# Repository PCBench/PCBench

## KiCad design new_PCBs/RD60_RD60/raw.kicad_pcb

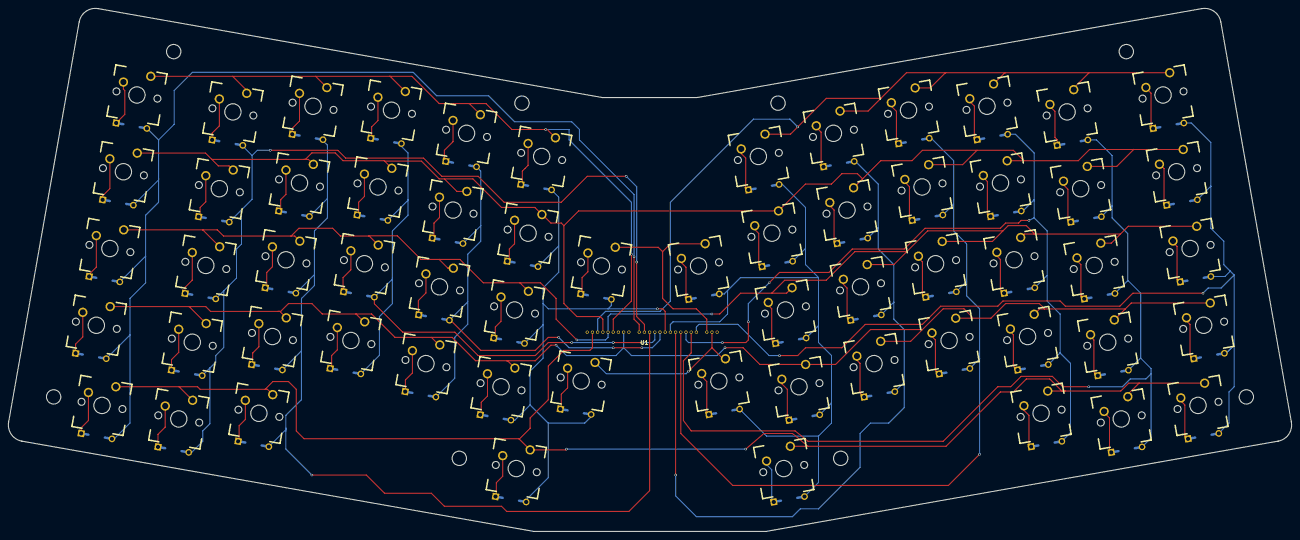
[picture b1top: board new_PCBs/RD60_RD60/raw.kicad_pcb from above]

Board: 2 copper layers, 313.6 x 127.8 mm, 61 parts (0 on the bottom side), 80 nets.

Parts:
U1: k270
U2, U3, U4, U5, U6, U7, U8, U9, U10, U11, U12, U13, U14, U15, U16, U17, U18, U19, U20, U21, U22, U23, U24, U25, U26, U27, U28, U29, U30, U31, U32, U33, U34, U35, U36, U37, U38, U39, U40, U41, U42, U43, U44, U45, U46, U47, U48, U49, U50, U51, U52, U53, U54, U55, U56, U57, U58, U59, U60, U61: mx1a

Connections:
2: U1.2, U6.1, U11.1, U16.1, U29.1, U34.1, U51.1, U56.1, U61.1
3: U1.3, U35.1, U39.1, U43.1, U47.1, U52.1, U57.1
4: U1.4, U3.1, U8.1, U13.1, U18.1, U22.1, U26.1, U36.1, U40.1, U44.1, U48.1, U53.1, U58.1
5: U1.5, U4.1, U9.1, U14.1, U19.1, U23.1, U27.1, U37.1, U41.1, U45.1, U49.1, U54.1, U59.1
6: U1.6, U2.1, U7.1, U12.1, U17.1, U21.1, U25.1
8: U1.8, U5.1, U10.1, U15.1, U20.1, U24.1, U28.1, U38.1, U42.1, U46.1, U50.1, U55.1, U60.1
10: U1.10, U2.2, U3.2, U4.2, U5.2, U6.2
11: U1.11, U7.2, U8.2, U9.2, U10.2, U11.2
12: U1.12, U12.2, U13.2, U14.2, U15.2, U16.2
13: U1.13, U17.2, U18.2, U19.2, U20.2
14: U1.14, U21.2, U22.2, U23.2, U24.2
15: U1.15, U25.2, U26.2, U27.2, U28.2, U29.2, U30.2, U31.2
16: U1.16, U32.2, U33.2, U34.2, U35.2, U36.2, U37.2, U38.2
17: U1.17, U39.2, U40.2, U41.2, U42.2
18: U1.18, U43.2, U44.2, U45.2, U46.2
19: U1.19, U47.2, U48.2, U49.2, U50.2, U51.2
20: U1.20, U52.2, U53.2, U54.2, U55.2, U56.2
21: U1.21, U57.2, U58.2, U59.2, U60.2, U61.2
22: U1.22, U30.1, U32.1
23: U1.23, U31.1, U33.1
unnamed: U2.3, U2.4
unnamed: U3.3, U3.4
unnamed: U4.3, U4.4
unnamed: U5.3, U5.4
unnamed: U6.3, U6.4
unnamed: U7.3, U7.4
unnamed: U8.3, U8.4
unnamed: U9.3, U9.4
unnamed: U10.3, U10.4
unnamed: U11.3, U11.4
unnamed: U12.3, U12.4
unnamed: U13.3, U13.4
unnamed: U14.3, U14.4
unnamed: U15.3, U15.4
unnamed: U16.3, U16.4
unnamed: U17.3, U17.4
unnamed: U18.3, U18.4
unnamed: U19.3, U19.4
unnamed: U20.3, U20.4
unnamed: U21.3, U21.4
unnamed: U22.3, U22.4
unnamed: U23.3, U23.4
unnamed: U24.3, U24.4
unnamed: U25.3, U25.4
unnamed: U26.3, U26.4
unnamed: U27.3, U27.4
unnamed: U28.3, U28.4
unnamed: U29.3, U29.4
unnamed: U30.3, U30.4
unnamed: U31.3, U31.4
unnamed: U32.3, U32.4
unnamed: U33.3, U33.4
unnamed: U34.3, U34.4
unnamed: U35.3, U35.4
unnamed: U36.3, U36.4
unnamed: U37.3, U37.4
unnamed: U38.3, U38.4
unnamed: U39.3, U39.4
unnamed: U40.3, U40.4
unnamed: U41.3, U41.4
unnamed: U42.3, U42.4
unnamed: U43.3, U43.4
unnamed: U44.3, U44.4
unnamed: U45.3, U45.4
unnamed: U46.3, U46.4
unnamed: U47.3, U47.4
unnamed: U48.3, U48.4
unnamed: U49.3, U49.4
unnamed: U50.3, U50.4
unnamed: U51.3, U51.4
unnamed: U52.3, U52.4
unnamed: U53.3, U53.4
unnamed: U54.3, U54.4
unnamed: U55.3, U55.4
unnamed: U56.3, U56.4
unnamed: U57.3, U57.4
unnamed: U58.3, U58.4
unnamed: U59.3, U59.4
unnamed: U60.3, U60.4
unnamed: U61.3, U61.4

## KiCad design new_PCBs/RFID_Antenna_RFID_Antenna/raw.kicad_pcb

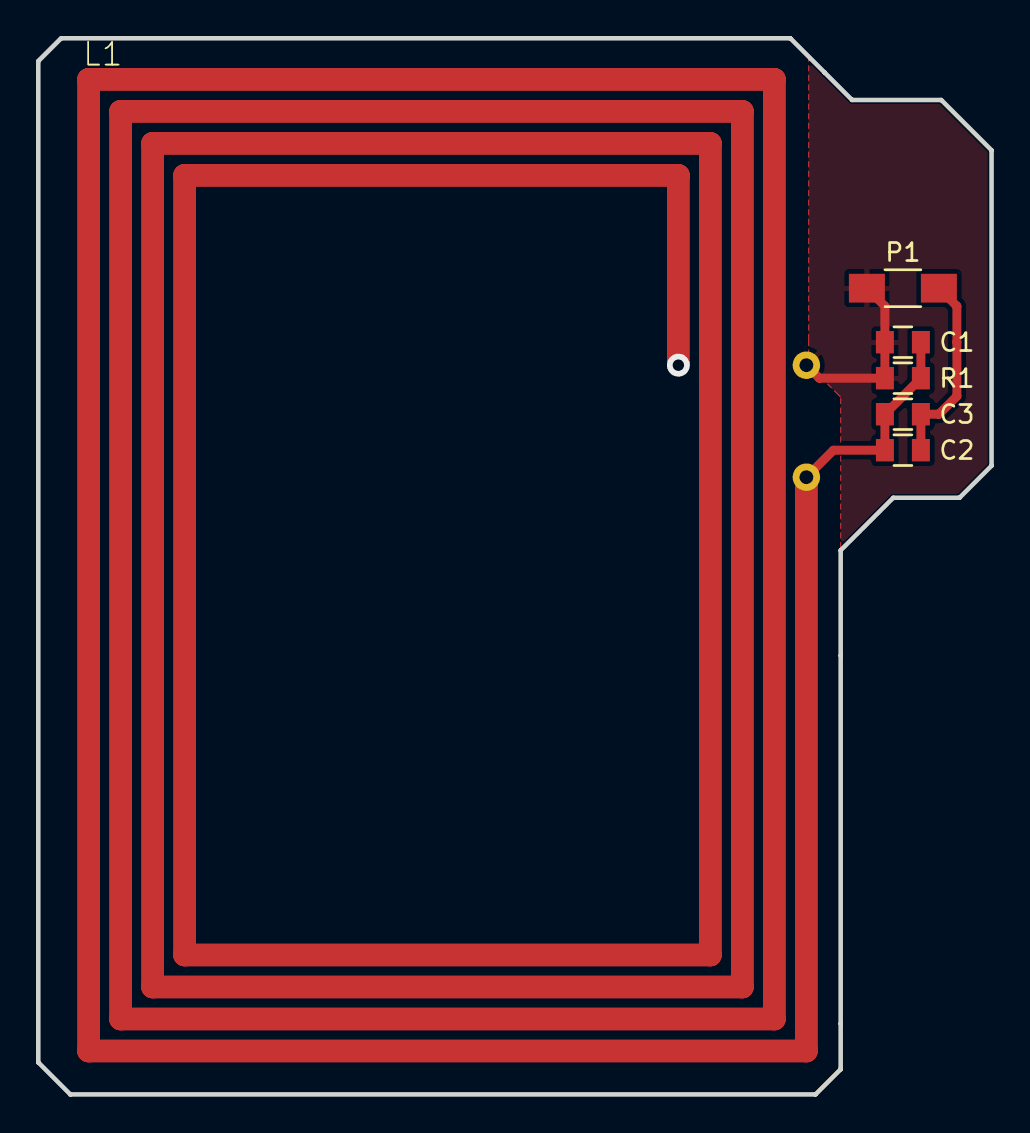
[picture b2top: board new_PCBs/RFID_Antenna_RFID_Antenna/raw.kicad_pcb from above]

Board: 2 copper layers, 53.0 x 58.7 mm, 6 parts (0 on the bottom side), 3 nets.

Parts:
C1, C2: 47p; C_0805
C3: 10p; C_0805
L1: 13.56 MHz Antenna; 13.56 RFID ANTENNA
P1: Coax; C_1206_HandSoldering
R1: 1k; C_0805

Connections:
unnamed: C1.1, L1.2, P1.2, R1.1
unnamed: C1.2, C2.1, C3.1, L1.1, R1.2
unnamed: C2.2, C3.2, P1.1

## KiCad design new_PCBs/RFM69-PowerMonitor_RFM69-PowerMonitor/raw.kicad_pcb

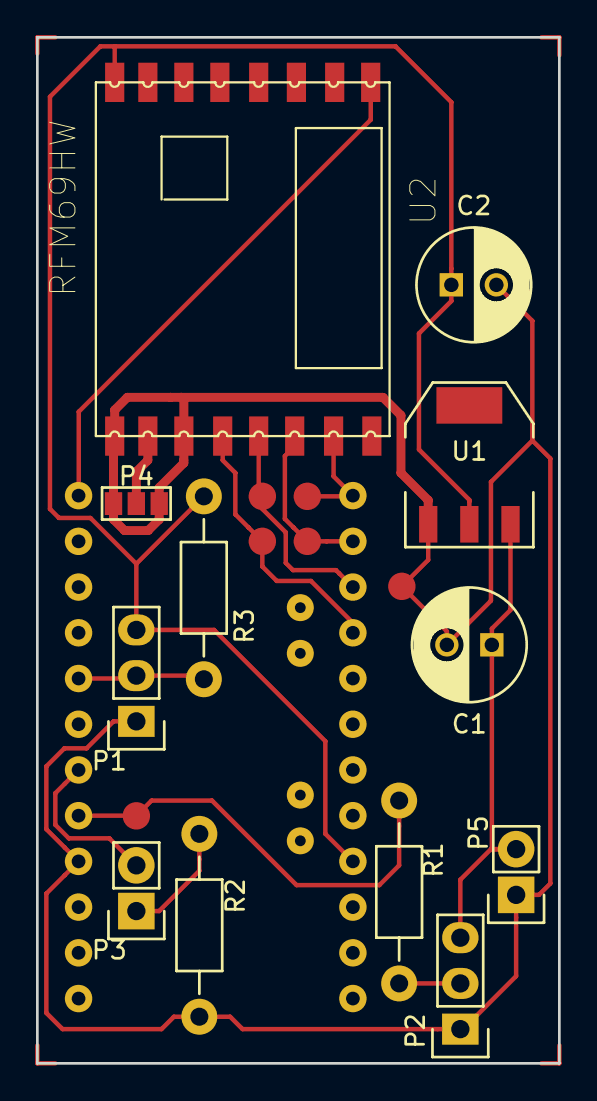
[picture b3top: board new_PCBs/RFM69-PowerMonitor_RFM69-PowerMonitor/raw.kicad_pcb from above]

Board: 2 copper layers, 29.0 x 57.0 mm, 13 parts (1 on the bottom side), 14 nets.

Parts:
C1: 10uF; C_Radial_D6.3_L11.2_P2.5
C2: 100uF; C_Radial_D6.3_L11.2_P2.5
P1: 1WIRE; Pin_Header_Straight_1x03
P2: CONN_PIR; Pin_Header_Straight_1x03
P3: MTR; Pin_Header_Straight_1x02
P4: ANT; GS3
P5: CONN_PWR; Pin_Header_Straight_1x02
R1, R2: 470; Resistor_Horizontal_RM10mm
R3: 2.2k; Resistor_Horizontal_RM10mm
U1: AP1117D33; SOT-223
U2: RFM69HW; RFM
uP1: ARDUPROMINI-6; ArduProMini-6

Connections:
+5V: C1.1, P2.3, P5.2, U1.3
GND: C1.2, C2.2, P1.1, P2.1, P4.1, P4.3, P5.1, R2.1, U1.1, U2.GNDA, U2.GNDB, uP1.10
unnamed: C2.1, P1.3, R3.1, U1.2, U2.VCC, uP1.22
unnamed: P1.2, R3.2, uP1.14
unnamed: P2.2, R1.2
unnamed: P3.1, R2.2
unnamed: P3.2, uP1.12
unnamed: P4.2, U2.ANT
unnamed: R1.1, uP1.11
unnamed: U2.MISO, uP1.28
unnamed: U2.MOSI, uP1.29
unnamed: U2.NSS, uP1.30
unnamed: U2.RESE, uP1.18
unnamed: U2.SCK, uP1.27

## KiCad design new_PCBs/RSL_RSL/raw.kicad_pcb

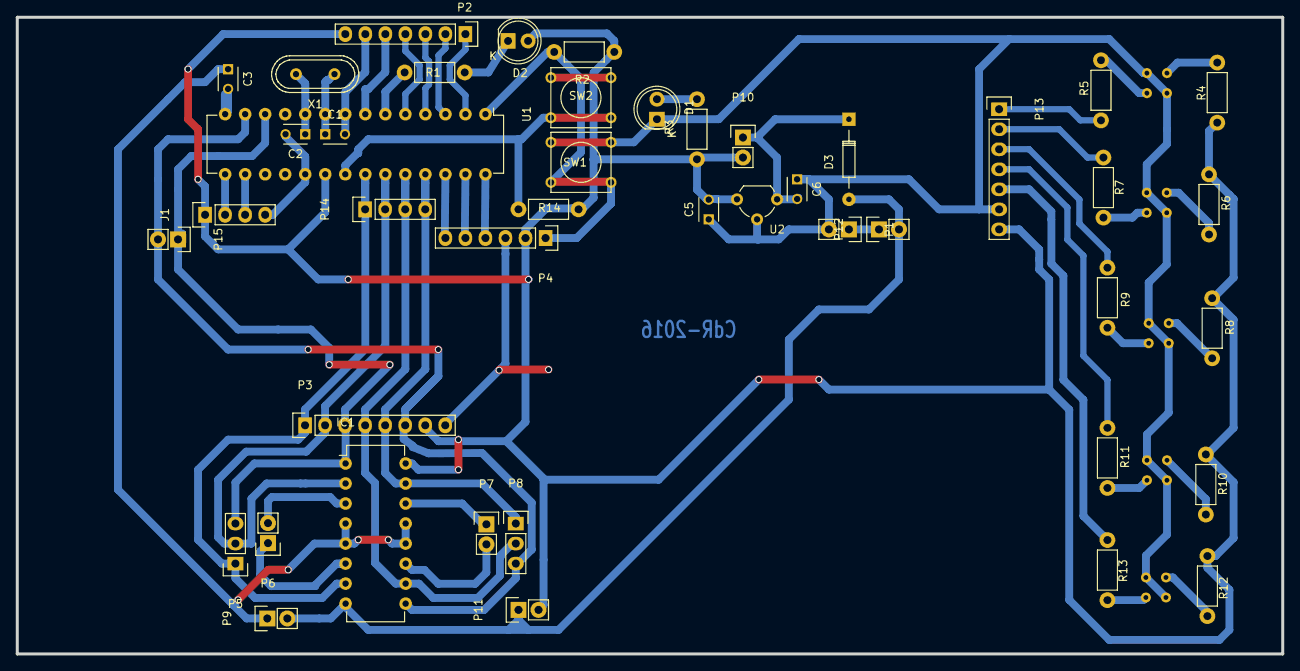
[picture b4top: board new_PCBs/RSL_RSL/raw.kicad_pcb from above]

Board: 2 copper layers, 160.5 x 80.8 mm, 49 parts (0 on the bottom side), 43 nets.

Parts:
C1: C-crsital; C_Disc_D3_P2.5
C2: C-cristal; C_Disc_D3_P2.5
C3: C; C_Disc_D3_P2.5
C5, C6: C-reg; C_Disc_D3_P2.5
D1: PWR; LED-5MM
D2: RUN; LED-5MM
D3: D_Small; Diode_DO-35_SOD27_Horizontal_RM10
IC1: L293D; DIP-16_W7.62mm
J1: USB; Pin_Header_Straight_1x04
P1: Alimentacion; Pin_Header_Straight_1x02
P2, P13: Pines_Sensores; Socket_Strip_Straight_1x07
P3: Pines_ Driver_M; Socket_Strip_Straight_1x08
P4: pickit; Socket_Strip_Straight_1x06
P5: 2A-1A-1.2E; Pin_Header_Straight_1x03
P6: motor1; Pin_Header_Straight_1x02
P7: motor2; Pin_Header_Straight_1x02
P8: E3.4-3A-4A; Pin_Header_Straight_1x03
P9: alimtacionMOTORES; Pin_Header_Straight_1x02
P10: BAT; Pin_Header_Straight_1x02
P11: jp1; Pin_Header_Straight_1x02
P12: PWRSW; Pin_Header_Straight_1x02
P14: Ctrl_Dir; Pin_Header_Straight_1x04
P15: PWM; Pin_Header_Straight_1x02
R1: 470; Resistor_Horizontal_RM7mm
R2: 10K; Resistor_Horizontal_RM7mm
R3, R4, R5, R6, R7, R8, R9, R10, R11, R12, R13, R14: R; Resistor_Horizontal_RM7mm
SW1: reset; SW_PUSH_SMALL
SW2: int0; SW_PUSH_SMALL
U1: PIC18F2550; DIP-28_W7.62mm
U2: 7805; TO-92_Molded_Wide
U3, U4, U5, U6, U7: CNY70; cny70-4
X1: CRYSTAL; Crystal_HC49-U_Vertical

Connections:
/0: R14.2, SW2.1, U1.21
/5: P4.6, U1.26
/6: P4.5, U1.27
/7: P4.4, U1.28
/D+: J1.3, U1.16
/D-: J1.2, U1.15
/driver_motores/1A: IC1.2, P3.2, P5.2, P14.2, U1.23
/driver_motores/2A: IC1.7, P3.1, P5.1, P14.1, U1.22
/driver_motores/3A: IC1.10, P3.4, P8.2, P14.3, U1.24
/driver_motores/4A: IC1.15, P3.5, P8.1, P14.4, U1.25
/driver_motores/E-1.2: IC1.1, P3.3, P5.3, P15.1, U1.12
/driver_motores/E-3.4: IC1.9, P3.6, P8.3, P15.2, U1.13
/r: P4.1, R2.2, SW1.2, U1.1
/run: R1.2, U1.6
/sensores/sens0: P2.1, P13.1, R5.1, U1.2
/sensores/sens1: P2.2, P13.2, R7.1, U1.3
/sensores/sens2: P2.3, P13.3, R9.1, U1.4
/sensores/sens3: P2.4, P13.4, R11.1, U1.5
/sensores/sens4: P2.5, P13.5, R13.1, U1.7
GND: C1.2, C2.2, C3.1, C5.1, C6.1, D1.1, IC1.4, IC1.5, IC1.12, IC1.13, J1.4, P1.2, P2.6, P3.8, P4.3, P9.1, P13.6, SW1.1, SW2.2, U1.8, U1.19, U2.2, U3.E, U3.K, U4.E, U4.K, U5.E, U5.K, U6.E, U6.K, U7.E, U7.K
unnamed: C1.1, U1.9, X1.1
unnamed: C2.1, U1.10, X1.2
unnamed: C3.2, U1.14
unnamed: C6.2, D3.1, P10.1, U2.1
unnamed: D1.2, R3.2
unnamed: D2.1, R1.1
unnamed: IC1.3, P6.2
unnamed: IC1.6, P6.1
unnamed: IC1.11, P7.2
unnamed: IC1.14, P7.1
unnamed: P1.1, P12.1
unnamed: R4.2, U3.A
unnamed: R5.2, U3.C
unnamed: R6.2, U4.A
unnamed: R7.2, U4.C
unnamed: R8.2, U5.A
unnamed: R9.2, U5.C
unnamed: R10.2, U6.A
unnamed: R11.2, U6.C
unnamed: R12.2, U7.A
unnamed: R13.2, U7.C
VCC: C5.2, D2.2, IC1.16, J1.1, P2.7, P3.7, P4.2, P10.2, P11.2, P13.7, R2.1, R3.1, R4.1, R6.1, R8.1, R10.1, R12.1, R14.1, U1.20, U2.3
VCC2: D3.2, IC1.8, P9.2, P11.1, P12.2

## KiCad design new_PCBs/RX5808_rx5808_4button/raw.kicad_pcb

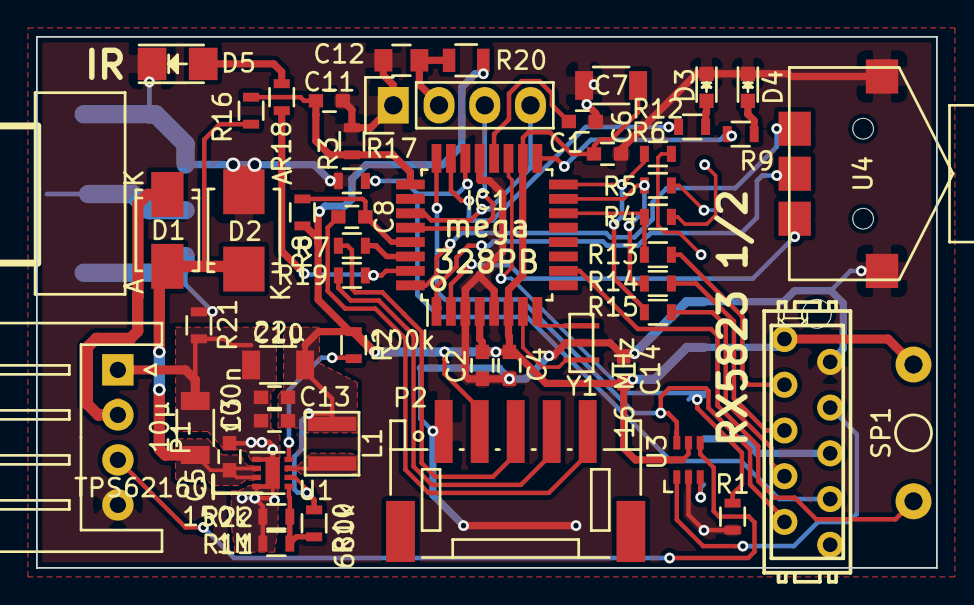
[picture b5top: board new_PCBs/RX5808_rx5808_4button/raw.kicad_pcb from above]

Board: 2 copper layers, 50.0 x 29.5 mm, 54 parts (1 on the bottom side), 47 nets.

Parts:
C1, C2, C3, C4, C6, C8, C9, C11, C13, C14: 100n; C_0603
C5: 10µ; C_1206
C7, C10: 22µ; C_1206
C12: 4,7u; C_0805
D1: B 140 F; SMA_Standard
D2: P6SMB 18A SMD; SMB_Standard
D3, D4: grün; LED_0603
D5: IR_EMITTER; LED_1206
IC1: ATMEGA328-A; TQFP-32_7x7mm_Pitch0.8mm
L1: 2,2µH 1,5A; NR3015
P1: CONN_01X04; JST_XH_S04B-XH-A_04x2.50mm_Angled
P2: CONN_01X05; JST_PH_S5B-PH-SM4-TB_05x2.00mm_Angled
P6: CONN_01X04; Pin_Header_Straight_1x04
P7: CONN_02X05; MICROMATCH-10
R1, R2, R3: 100k; R_0603
R4, R5, R6, R7, R13, R14, R15, R17, R19: 1k; R_0603
R8: 10k; R_0603
R9, R12: 220; R_0603
R10: 680k; R_0603
R11: 1M; R_0603
R16: 15k; R_0603
R18: 100; R_0603
R20: 10; R_0805
R21: brücke; R_0603
R22: 150k; R_0603
SMA_E1: SMA_EDGE; SMA_EDGE_Johnson_142-0701-801
SP1: BUZ; Buzzer_12x9.5RM7.6
U1: TPS62160; DFN-8-1EP_2x2mm_Pitch0.5mm
U2: RX5808
U3: sn74lvc1g3157; SC-70-6
U4: MCPL3-BC-V; MCPL3-AC-V
Y1: 16 MHz; CerOsc_3,2x1,3

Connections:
+5V: C2.1, C4.1, C6.1, C7.1, C9.1, C10.1, C13.1, C14.1, IC1.4, IC1.6, IC1.18, L1.2, P2.2, P7.1, R2.2, R8.1, R10.1, R20.2, SP1.1, U1.6, U2.8, U3.5
+12V: C3.1, C5.1, D1.2, D2.1, R16.2, U1.2, U1.3
/Audio1: P7.6, U2.10
/DTR: C8.2, P2.5
/Funk1_clk: R6.1, U2.6
/Funk1_data: R4.1, U2.4
/Funk1_ss: R5.1, U2.5
/Funk2_clk: P7.7, R15.1
/Funk2_data: P7.3, R13.1
/Funk2_ss: P7.5, R14.1
/VidOut: P1.3, U3.4
/Video1: U2.11, U3.3
/Video2: P7.4, U3.1
/adc_12V: C11.1, IC1.25, R16.1, R17.2
/buzzer: IC1.10, SP1.2
/down: IC1.2, U4.2
/led1: IC1.23, R12.2
/led2: IC1.24, P7.9, U3.6
/led3: IC1.17, R9.2
/miso: IC1.16, R6.2, R15.2
/mode: IC1.1, U4.3
/mosi: IC1.15, R5.2, R14.2
/reset: C8.1, IC1.29, R8.2
/rssi1: IC1.19, R1.1, U2.9
/rssi2: IC1.22, P7.8, R3.1
/rxd: P2.3, R7.1
/scl: IC1.28, P6.3
/sda: IC1.27, P6.4
/ss: IC1.14, R4.2, R13.2
/txd: P2.4, R19.2
/up: IC1.32, U4.1
GND: C1.2, C2.2, C4.2, C6.2, C7.2, C11.2, C12.2, C14.2, D2.2, D3.1, D4.1, D5.1, IC1.3, IC1.5, IC1.21, P1.4, P2.1, P6.1, P7.2, R1.2, R3.2, R17.1, R21.2, SMA_E1.0, SMA_E1.2, U2.1, U2.3, U2.7, U2.12, U3.2, U4.4, U4.5, Y1.2
GNDPWR: C3.2, C5.2, C9.2, C10.2, C13.2, P1.1, R11.2, R21.1, R22.2, U1.1, U1.4, U1.EP
unnamed: C1.1, IC1.20
unnamed: C12.1, P6.2, R20.1
unnamed: D1.1, P1.2
unnamed: D3.2, R12.1
unnamed: D4.2, R9.1
unnamed: D5.2, R18.2
unnamed: IC1.7, Y1.3
unnamed: IC1.8, Y1.1
unnamed: IC1.30, R7.2
unnamed: IC1.31, R18.1, R19.1
unnamed: L1.1, U1.7
unnamed: R2.1, U1.8
unnamed: R10.2, R11.1, R22.1, U1.5
unnamed: SMA_E1.1, U2.2

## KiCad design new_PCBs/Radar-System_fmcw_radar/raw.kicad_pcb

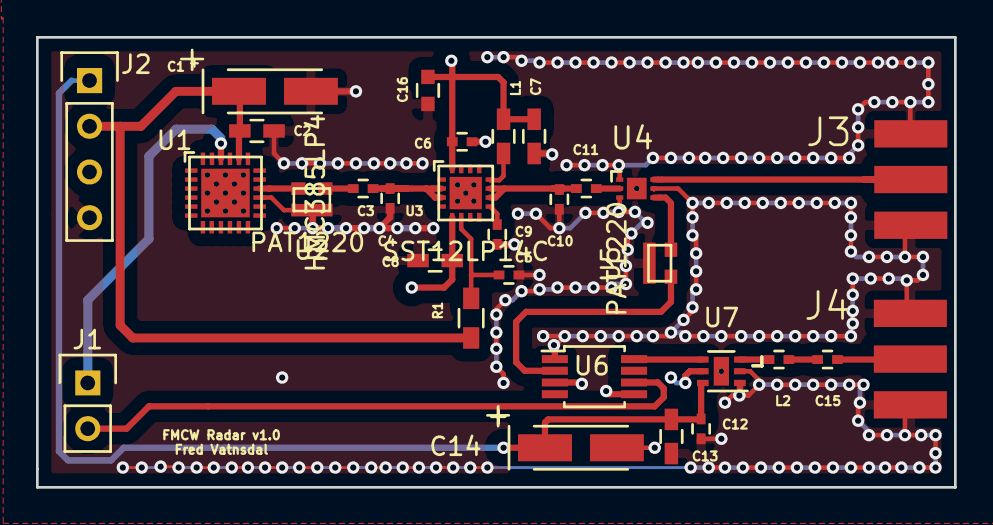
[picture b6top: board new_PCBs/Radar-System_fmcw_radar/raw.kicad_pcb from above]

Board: 4 copper layers, 51.0 x 25.0 mm, 30 parts (0 on the bottom side), 21 nets.

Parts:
C1: 4.7uF; TantalC_SizeA_EIA-3216_HandSoldering
C2, C13: 10nF; C_0603_HandSoldering
C3, C11: 47pF; C_0402
C4: 1.2pF; C_0402
C5, C6: 100pF; C_0402
C7, C8: 0.1uF; C_0603_HandSoldering
C9: 10pF; C_0402
C10: 2.0pF; C_0402
C12: 1nF; C_0402
C14: 2.2uF; TantalC_SizeA_EIA-3216_HandSoldering
C15: 2.7pF; C_0402
C16: 10uF; C_0603
J1: conn_2; Pin_Header_Straight_1x02
J2: conn_4; Pin_Header_Straight_1x04
J3, J4: conn_sma; CONSMA003.062
L1: 12nH; C_0603_HandSoldering
L2: 2.0nH; C_0402
R1: 30; R_0603_HandSoldering
U1: HMC385LP4; VQFN-24
U2, U5: PAT1220
U3: SST12LP14C; VQFN-16
U4: SKY16406-381LF; SOIC-6
U6: HMC272AMS8; MSOP-8_3x3mm_Pitch0.65mm
U7: HMC667LP2; DFN-6_2x2

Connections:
/3.3V: C6.1, C7.1, C8.1, C16.1, J2.3, L1.1, U3.5, U3.16
/3V: C1.1, C2.1, J2.2, R1.1, U1.20
/3V/5V: C12.1, C13.1, C14.1, J2.1, U7.6
/IF_OUT: J1.2, U6.6
/VTUNE: J1.1, U1.22
GND: C1.2, C2.2, C4.2, C5.2, C6.2, C7.2, C8.2, C9.2, C10.2, C12.2, C13.2, C14.2, C16.2, J2.4, J3.2, J4.2, U1.15, U1.PAD, U2.3, U3.PAD, U4.1, U4.3, U4.5, U4.PAD, U5.3, U6.1, U6.3, U6.5, U7.1, U7.2, U7.5, U7.PAD
unnamed: C3.1, C4.1, U3.2, U3.3
unnamed: C3.2, U2.2
unnamed: C5.1, R1.2, U3.6
unnamed: C9.1, U3.9
unnamed: C10.1, C11.2, U3.10, U3.11
unnamed: C11.1, U4.2
unnamed: C15.1, J4.1
unnamed: C15.2, L2.2
unnamed: J3.1, U4.6
unnamed: L1.2, U3.12
unnamed: L2.1, U7.3
unnamed: U1.16, U2.1
unnamed: U4.4, U5.1
unnamed: U5.2, U6.2
unnamed: U6.8, U7.4
